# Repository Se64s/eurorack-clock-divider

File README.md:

# eurorack-clock-divider

Clock divider based on [Divide &amp; Conquer](https://www.nonlinearcircuits.com/modules/p/divide-and-conquer) from NONLINEARCIRCUITS.

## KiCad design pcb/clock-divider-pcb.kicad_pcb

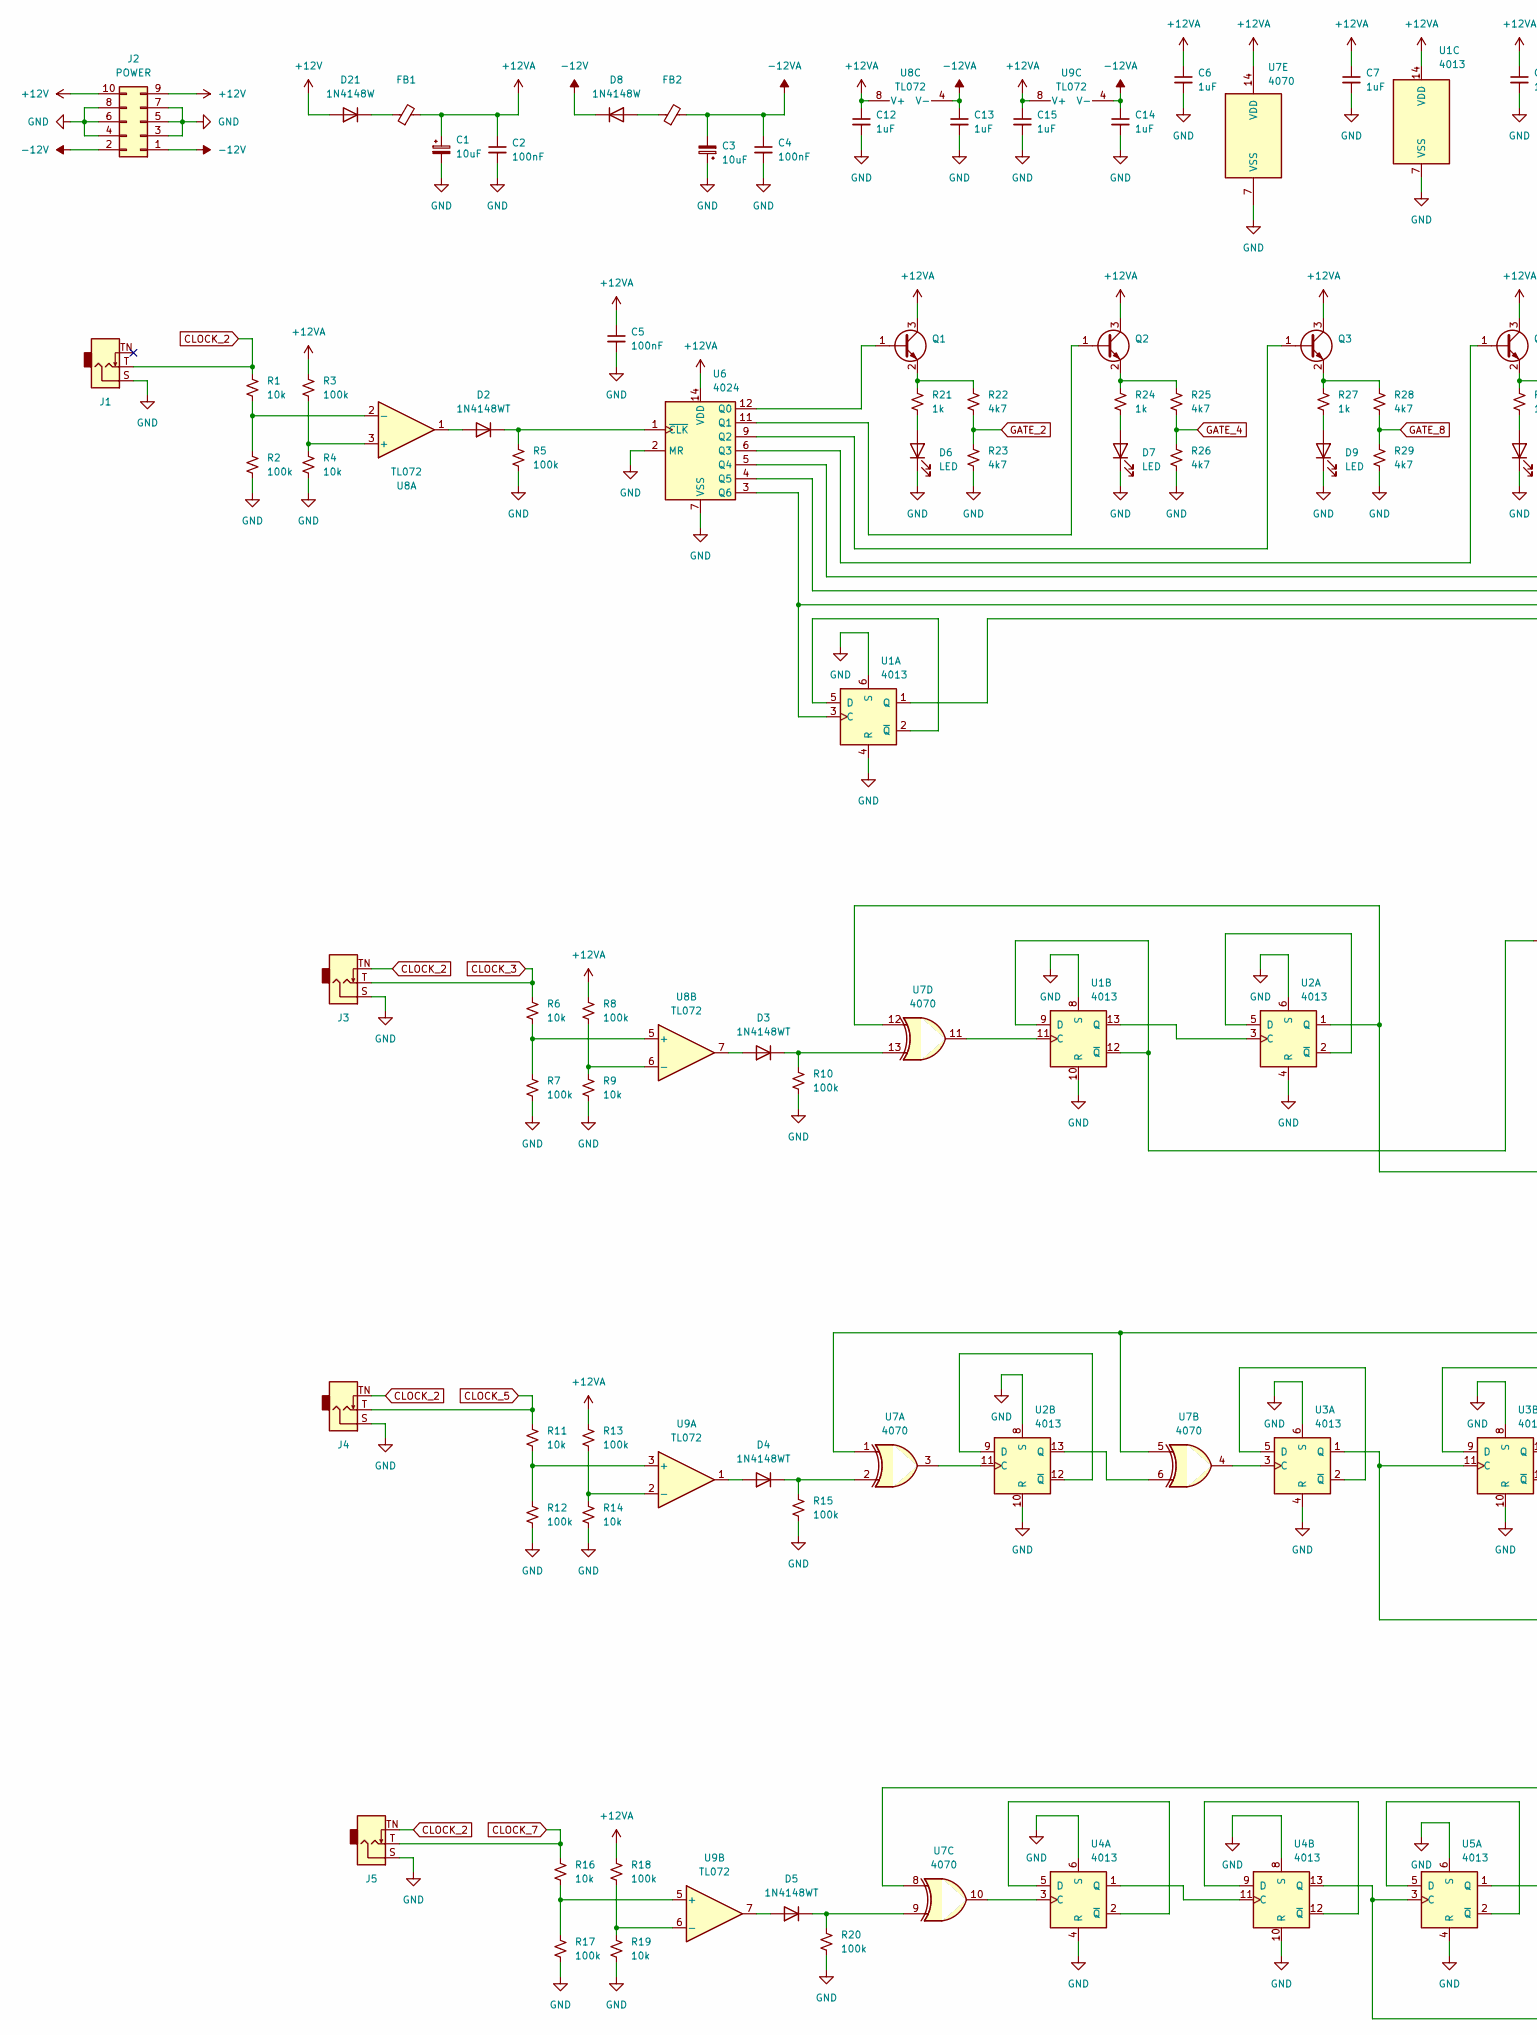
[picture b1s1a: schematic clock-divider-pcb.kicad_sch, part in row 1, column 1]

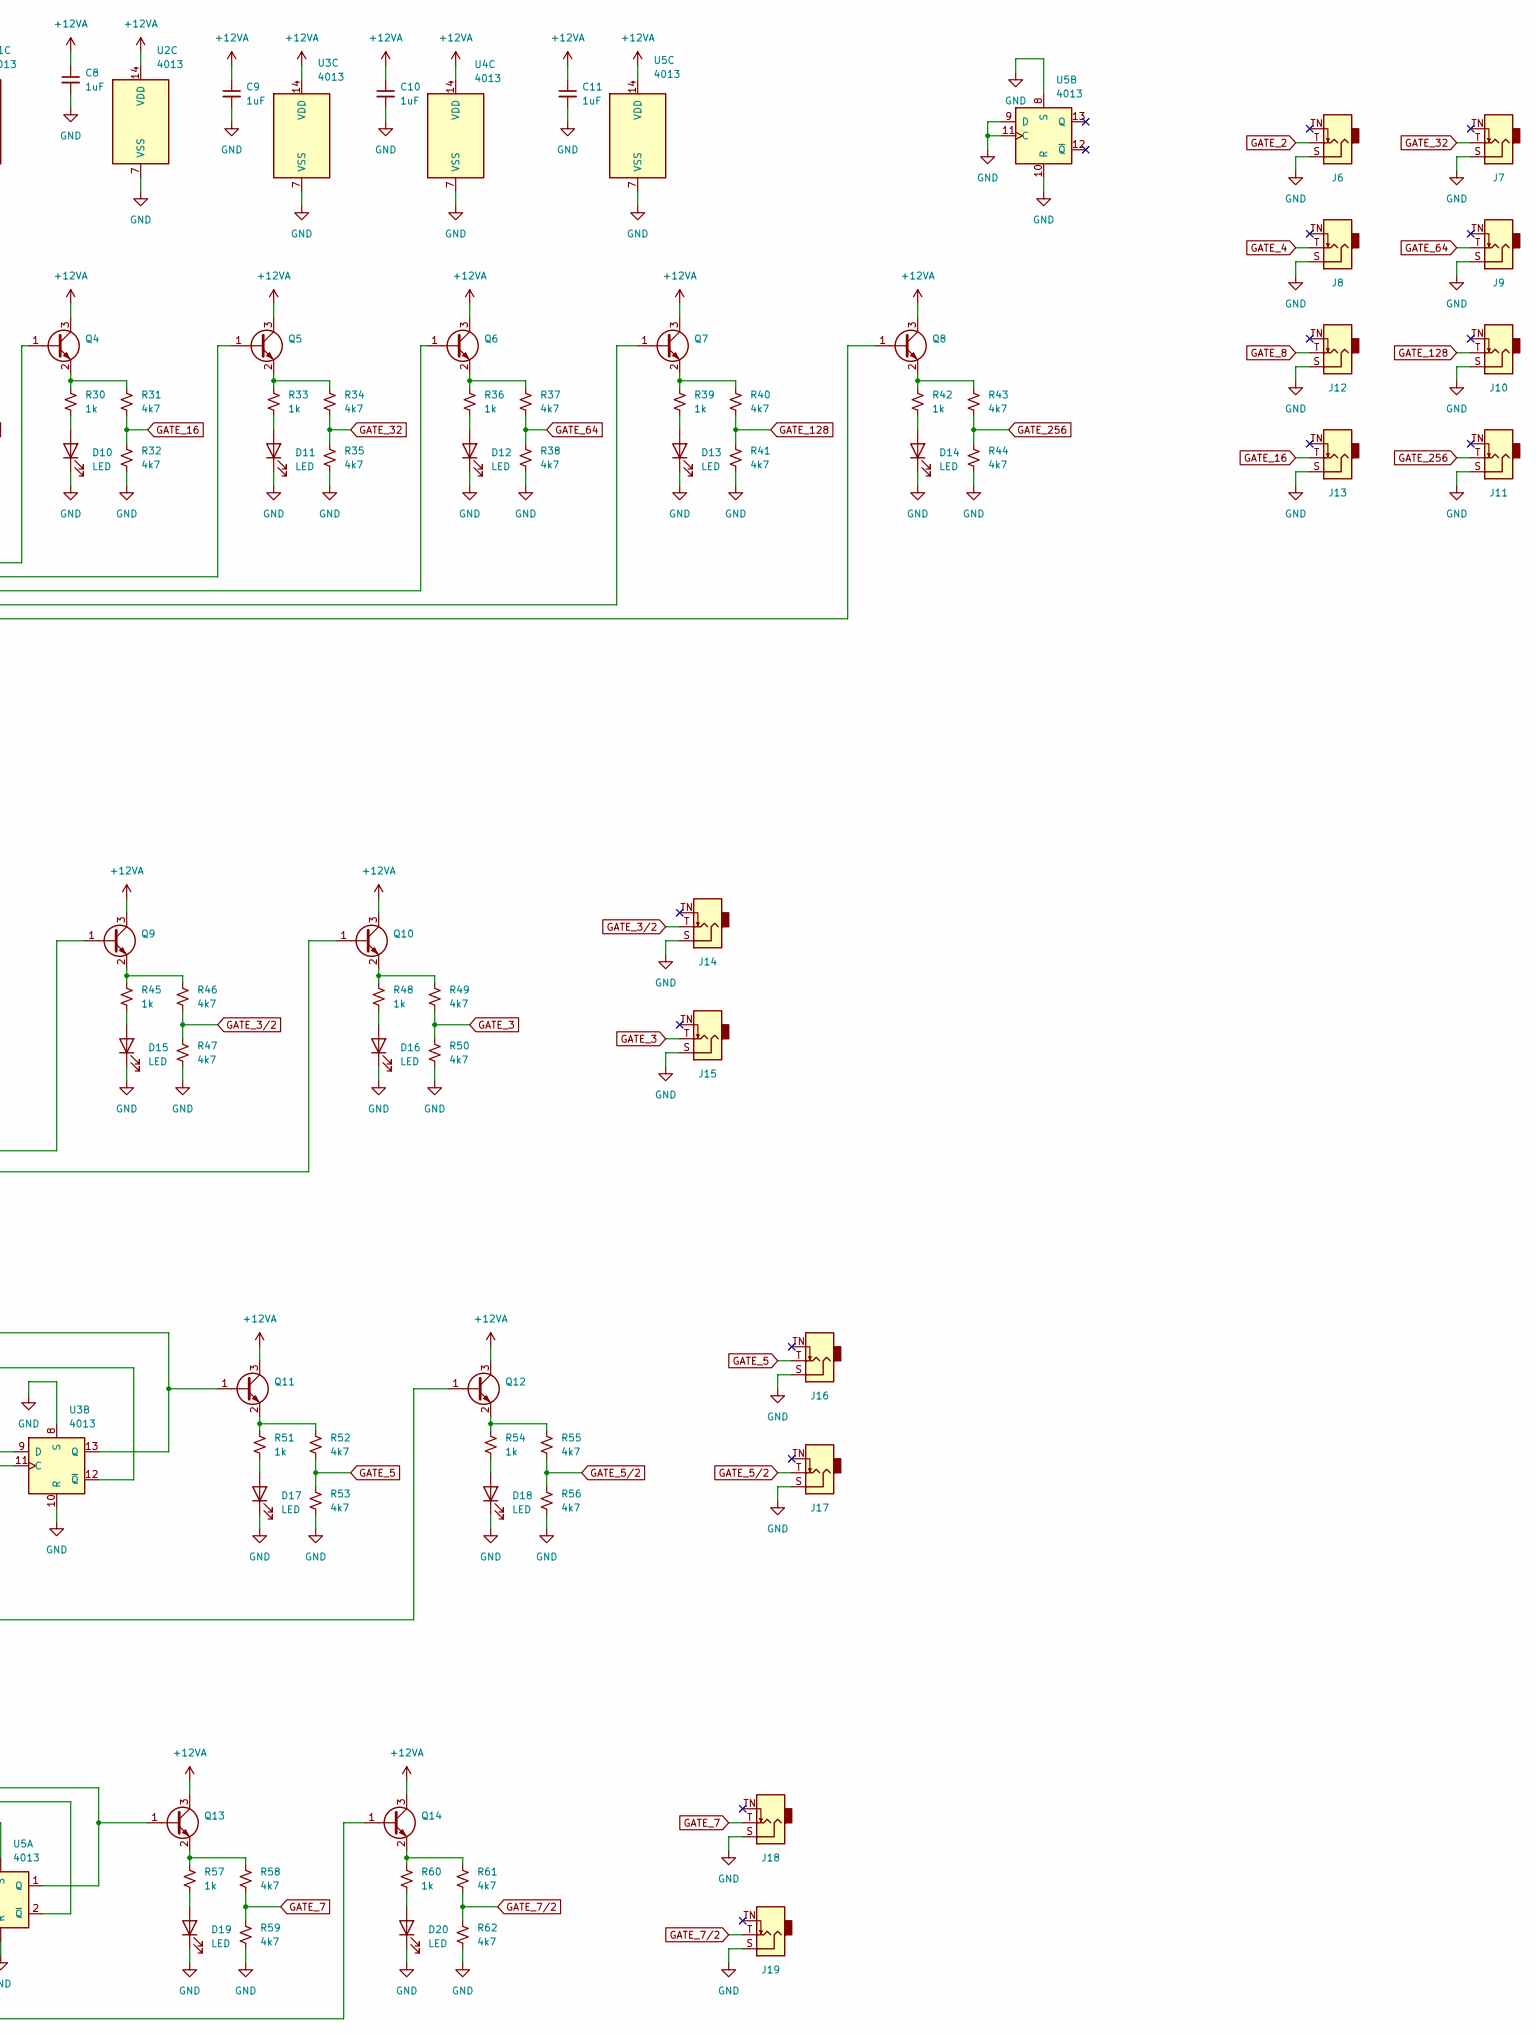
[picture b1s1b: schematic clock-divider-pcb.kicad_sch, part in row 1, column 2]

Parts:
C1, C3: 10uF; CP_Elec_4x5.4
C2, C4, C5: 100nF; C_0805_2012Metric_Pad1.18x1.45mm_HandSolder
C6, C7, C8, C9, C10, C11, C12, C13, C14, C15: 1uF; C_0805_2012Metric_Pad1.18x1.45mm_HandSolder
D2, D3, D4, D5: 1N4148WT; D_SOD-523
D6, D7, D9, D10, D11, D12, D13, D14, D15, D16, D17, D18, D19, D20: LED; LED_0402_1005Metric_Pad0.77x0.64mm_HandSolder
D8, D21: 1N4148W; D_SOD-123
FB1, FB2: FerriteBead_Small; L_0805_2012Metric_Pad1.05x1.20mm_HandSolder
J1, J3, J4, J5, J6, J7, J8, J9, J10, J11, J12, J13, J14, J15, J16, J17, J18, J19: AudioJack2_SwitchT; Jack_3.5mm_QingPu_WQP-PJ398SM_Vertical_CircularHoles
J2: POWER; IDC-Header_2x05_P2.54mm_Vertical
Q1, Q2, Q3, Q4, Q5, Q6, Q7, Q8, Q9, Q10, Q11, Q12, Q13, Q14: MMBT3904; SOT-23
R1, R4, R6, R9, R11, R14, R16, R19: 10k; R_0603_1608Metric_Pad0.98x0.95mm_HandSolder
R2, R3, R5, R7, R8, R10, R12, R13, R15, R17, R18, R20: 100k; R_0603_1608Metric_Pad0.98x0.95mm_HandSolder
R21, R24, R27, R30, R33, R36, R39, R42, R45, R48, R51, R54, R57, R60: 1k; R_0603_1608Metric_Pad0.98x0.95mm_HandSolder
R22, R23, R25, R26, R28, R29, R31, R32, R34, R35, R37, R38, R40, R41, R43, R44, R46, R47, R49, R50, R52, R53, R55, R56, R58, R59, R61, R62: 4k7; R_0603_1608Metric_Pad0.98x0.95mm_HandSolder
U1, U2, U3, U4, U5: 4013; SOIC-14_3.9x8.7mm_P1.27mm
U6: 4024; SOIC-14_3.9x8.7mm_P1.27mm
U7: 4070; SOIC-14_3.9x8.7mm_P1.27mm
U8, U9: TL072; SOIC-8_3.9x4.9mm_P1.27mm

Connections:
+12V: D21.2 (A), J2.9, J2.10
+12VA: C1.1, C2.1, C5.1, C6.1, C7.1, C8.1, C9.1, C10.1, C11.1, C12.1, C15.1, FB1.2, Q1.3 (C), Q2.3 (C), Q3.3 (C), Q4.3 (C), Q5.3 (C), Q6.3 (C), Q7.3 (C), Q8.3 (C), Q9.3 (C), Q10.3 (C), Q11.3 (C), Q12.3 (C), Q13.3 (C), Q14.3 (C), R3.1, R8.1, R13.1, R18.1, U1.14 (VDD), U2.14 (VDD), U3.14 (VDD), U4.14 (VDD), U5.14 (VDD), U6.14 (VDD), U7.14 (VDD), U8.8 (V+), U9.8 (V+)
-12V: D8.1 (K), J2.1, J2.2
-12VA: C3.2, C4.1, C13.1, C14.1, FB2.2, U8.4 (V-), U9.4 (V-)
CLOCK_2: J1.T, J3.TN, J4.TN, J5.TN, R1.1
CLOCK_3: J3.T, R6.1
CLOCK_5: J4.T, R11.1
CLOCK_7: J5.T, R16.1
GATE_2: J6.T, R22.2, R23.1
GATE_3: J15.T, R49.2, R50.1
GATE_3/2: J14.T, R46.2, R47.1
GATE_4: J8.T, R25.2, R26.1
GATE_5: J16.T, R52.2, R53.1
GATE_5/2: J17.T, R55.2, R56.1
GATE_7: J18.T, R58.2, R59.1
GATE_7/2: J19.T, R61.2, R62.1
GATE_8: J12.T, R28.2, R29.1
GATE_16: J13.T, R31.2, R32.1
GATE_32: J7.T, R34.2, R35.1
GATE_64: J9.T, R37.2, R38.1
GATE_128: J10.T, R40.2, R41.1
GATE_256: J11.T, R43.2, R44.1
GND: C1.2, C2.2, C3.1, C4.2, C5.2, C6.2, C7.2, C8.2, C9.2, C10.2, C11.2, C12.2, C13.2, C14.2, C15.2, D6.1 (K), D7.1 (K), D9.1 (K), D10.1 (K), D11.1 (K), D12.1 (K), D13.1 (K), D14.1 (K), D15.1 (K), D16.1 (K), D17.1 (K), D18.1 (K), D19.1 (K), D20.1 (K), J1.S, J2.3, J2.4, J2.5, J2.6, J2.7, J2.8, J3.S, J4.S, J5.S, J6.S, J7.S, J8.S, J9.S, J10.S, J11.S, J12.S, J13.S, J14.S, J15.S, J16.S, J17.S, J18.S, J19.S, R2.2, R4.2, R5.2, R7.2, R9.2, R10.2, R12.2, R14.2, R15.2, R17.2, R19.2, R20.2, R23.2, R26.2, R29.2, R32.2, R35.2, R38.2, R41.2, R44.2, R47.2, R50.2, R53.2, R56.2, R59.2, R62.2, U1.4 (R), U1.6 (S), U1.7 (VSS), U1.8 (S), U1.10 (R), U2.4 (R), U2.6 (S), U2.7 (VSS), U2.8 (S), U2.10 (R), U3.4 (R), U3.6 (S), U3.7 (VSS), U3.8 (S), U3.10 (R), U4.4 (R), U4.6 (S), U4.7 (VSS), U4.8 (S), U4.10 (R), U5.4 (R), U5.6 (S), U5.7 (VSS), U5.8 (S), U5.9 (D), U5.10 (R), U5.11 (C), U6.2 (MR), U6.7 (VSS), U7.7 (VSS)
unnamed: D2.2 (A), U8.1
unnamed: D2.1 (K), R5.1, U6.1 (~CLK)
unnamed: D3.2 (A), U8.7
unnamed: D3.1 (K), R10.1, U7.13
unnamed: D4.2 (A), U9.1
unnamed: D4.1 (K), R15.1, U7.2
unnamed: D5.2 (A), U9.7
unnamed: D5.1 (K), R20.1, U7.9
unnamed: D6.2 (A), R21.2
unnamed: D7.2 (A), R24.2
unnamed: D8.2 (A), FB2.1
unnamed: D9.2 (A), R27.2
unnamed: D10.2 (A), R30.2
unnamed: D11.2 (A), R33.2
unnamed: D12.2 (A), R36.2
unnamed: D13.2 (A), R39.2
unnamed: D14.2 (A), R42.2
unnamed: D15.2 (A), R45.2
unnamed: D16.2 (A), R48.2
unnamed: D17.2 (A), R51.2
unnamed: D18.2 (A), R54.2
unnamed: D19.2 (A), R57.2
unnamed: D20.2 (A), R60.2
unnamed: D21.1 (K), FB1.1
unnamed: Q1.1 (B), U6.12 (Q0)
unnamed: Q1.2 (E), R21.1, R22.1
unnamed: Q2.1 (B), U6.11 (Q1)
unnamed: Q2.2 (E), R24.1, R25.1
unnamed: Q3.1 (B), U6.9 (Q2)
unnamed: Q3.2 (E), R27.1, R28.1
unnamed: Q4.1 (B), U6.6 (Q3)
unnamed: Q4.2 (E), R30.1, R31.1
unnamed: Q5.1 (B), U6.5 (Q4)
unnamed: Q5.2 (E), R33.1, R34.1
unnamed: Q6.1 (B), U6.4 (Q5)
unnamed: Q6.2 (E), R36.1, R37.1
unnamed: Q7.1 (B), U1.3 (C), U6.3 (Q6)
unnamed: Q7.2 (E), R39.1, R40.1
unnamed: Q8.1 (B), U1.1 (Q)
unnamed: Q8.2 (E), R42.1, R43.1
unnamed: Q9.1 (B), U1.9 (D), U1.12 (~Q)
unnamed: Q9.2 (E), R45.1, R46.1
unnamed: Q10.1 (B), U2.1 (Q), U7.12
unnamed: Q10.2 (E), R48.1, R49.1
unnamed: Q11.1 (B), U3.13 (Q), U7.1, U7.5
unnamed: Q11.2 (E), R51.1, R52.1
unnamed: Q12.1 (B), U3.1 (Q), U3.11 (C)
unnamed: Q12.2 (E), R54.1, R55.1
unnamed: Q13.1 (B), U5.1 (Q), U7.8
unnamed: Q13.2 (E), R57.1, R58.1
unnamed: Q14.1 (B), U4.13 (Q), U5.3 (C)
unnamed: Q14.2 (E), R60.1, R61.1
unnamed: U1.2 (~Q), U1.5 (D)
unnamed: U1.11 (C), U7.11
unnamed: U1.13 (Q), U2.3 (C)
unnamed: U2.2 (~Q), U2.5 (D)
unnamed: U2.11 (C), U7.3
unnamed: U2.9 (D), U2.12 (~Q)
unnamed: U2.13 (Q), U7.6
unnamed: U3.3 (C), U7.4
unnamed: U3.2 (~Q), U3.5 (D)
unnamed: U3.9 (D), U3.12 (~Q)
unnamed: U4.3 (C), U7.10
unnamed: U4.2 (~Q), U4.5 (D)
unnamed: U4.1 (Q), U4.11 (C)
unnamed: U4.9 (D), U4.12 (~Q)
unnamed: U5.2 (~Q), U5.5 (D)
unnamed: R3.2, R4.1, U8.3 (+)
unnamed: R1.2, R2.1, U8.2 (-)
unnamed: R6.2, R7.1, U8.5 (+)
unnamed: R8.2, R9.1, U8.6 (-)
unnamed: R11.2, R12.1, U9.3 (+)
unnamed: R13.2, R14.1, U9.2 (-)
unnamed: R16.2, R17.1, U9.5 (+)
unnamed: R18.2, R19.1, U9.6 (-)

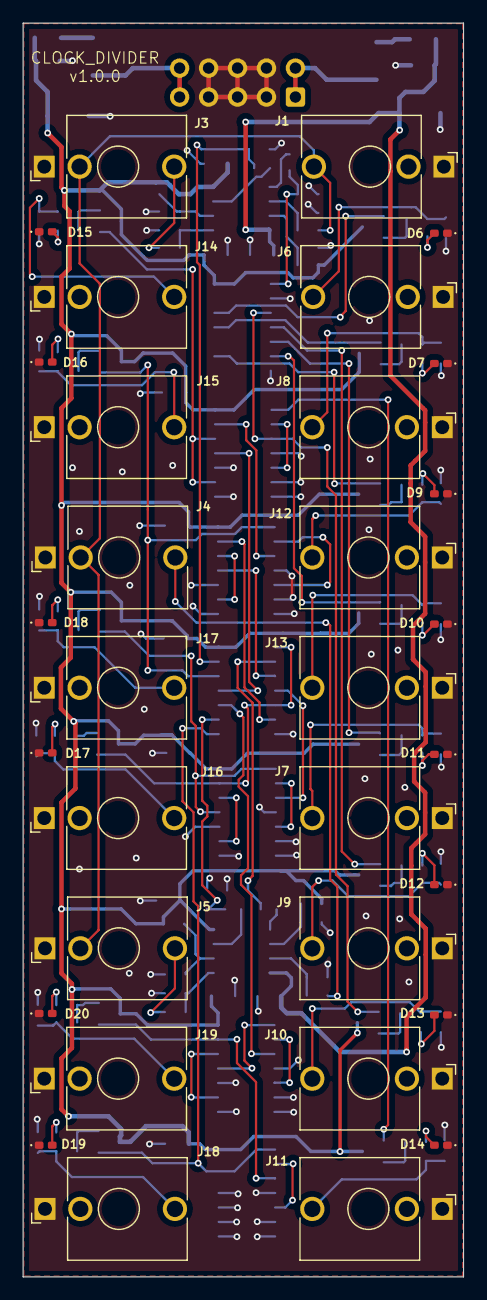
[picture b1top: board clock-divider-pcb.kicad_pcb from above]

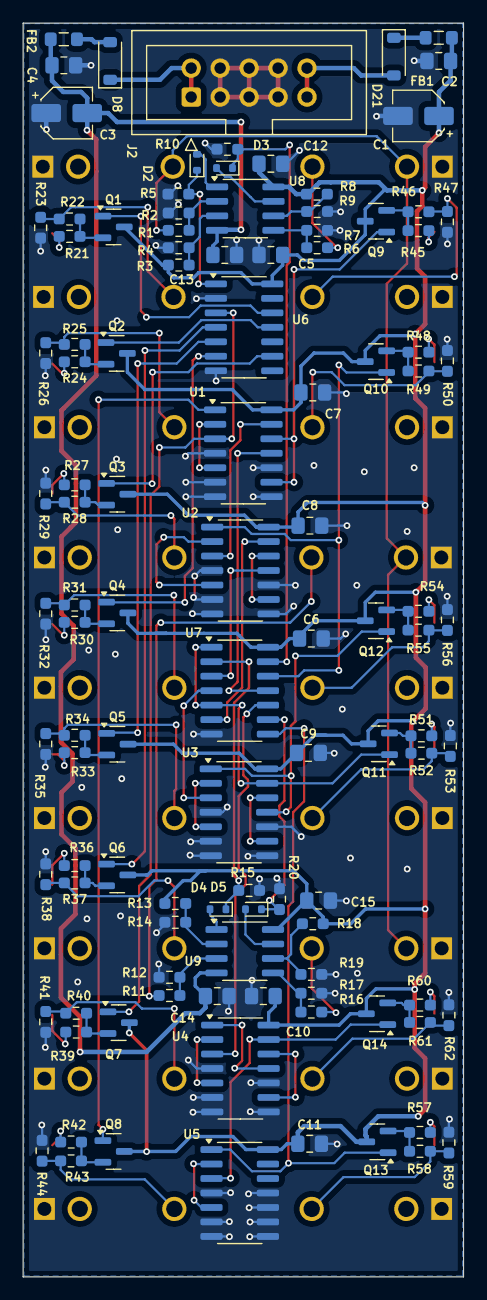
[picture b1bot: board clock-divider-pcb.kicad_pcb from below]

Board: 2 copper layers, 38.6 x 110.0 mm, 141 parts (109 on the bottom side), 98 nets.

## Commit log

2025-10-06 feat: add first version before fab
